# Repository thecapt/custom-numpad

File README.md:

# custom-numpad
My first keyboard pcb for a standard numpad layout. Uses a 4x5 array of MX Cherry compatable switches for better customisability over a standard 17-key numpad.
The design is based on the [discipad](https://github.com/coseyfannitutti/discipad) but was modified to use a full array and a Pro Micro 5V.

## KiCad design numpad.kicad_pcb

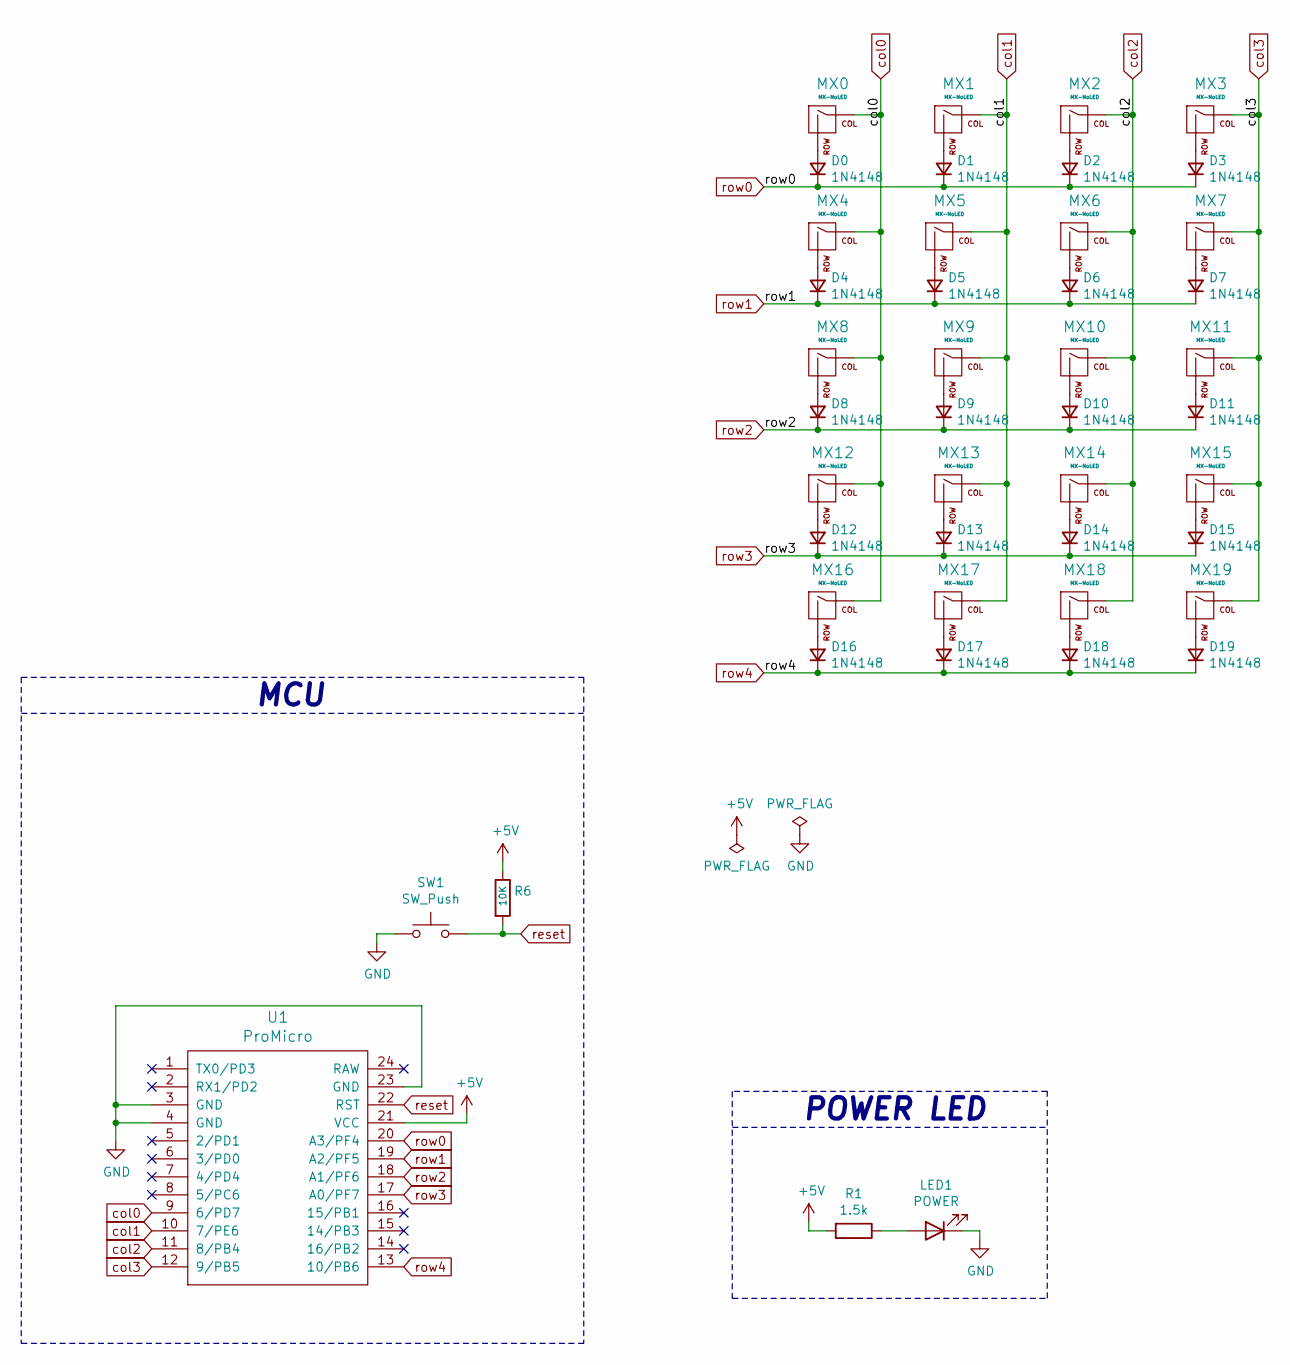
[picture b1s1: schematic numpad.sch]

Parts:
D0, D1, D2, D3, D4, D5, D6, D7, D8, D9, D10, D11, D12, D13, D14, D15, D16, D17, D18, D19: 1N4148; D_DO-35_SOD27_P5.08mm_Horizontal
LED1: POWER; LED_D3.0mm
MX0, MX1, MX2, MX3, MX4, MX5, MX6, MX7, MX8, MX9, MX10, MX11, MX12, MX13, MX14, MX15, MX16, MX17, MX18, MX19: MX-NoLED; SW_Cherry_MX_1.00u_PCB
R1: 1.5k; R_Axial_DIN0207_L6.3mm_D2.5mm_P7.62mm_Horizontal
R6: 10K; R_Axial_DIN0207_L6.3mm_D2.5mm_P7.62mm_Horizontal
SW1: SW_Push; SW_PUSH_6mm
U1: ProMicro; ArduinoProMicro

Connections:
+5V: R1.2, R6.1, U1.21 (VCC)
GND: LED1.1 (K), SW1.1, U1.3 (GND), U1.4 (GND), U1.23 (GND)
unnamed: D0.2 (A), MX0.2 (ROW)
unnamed: D1.2 (A), MX1.2 (ROW)
unnamed: D2.2 (A), MX2.2 (ROW)
unnamed: D3.2 (A), MX3.2 (ROW)
unnamed: D4.2 (A), MX4.2 (ROW)
unnamed: D5.2 (A), MX5.2 (ROW)
unnamed: D6.2 (A), MX6.2 (ROW)
unnamed: D7.2 (A), MX7.2 (ROW)
unnamed: D8.2 (A), MX8.2 (ROW)
unnamed: D9.2 (A), MX9.2 (ROW)
unnamed: D10.2 (A), MX10.2 (ROW)
unnamed: D11.2 (A), MX11.2 (ROW)
unnamed: D12.2 (A), MX12.2 (ROW)
unnamed: D13.2 (A), MX13.2 (ROW)
unnamed: D14.2 (A), MX14.2 (ROW)
unnamed: D15.2 (A), MX15.2 (ROW)
unnamed: D16.2 (A), MX16.2 (ROW)
unnamed: D17.2 (A), MX17.2 (ROW)
unnamed: D18.2 (A), MX18.2 (ROW)
unnamed: D19.2 (A), MX19.2 (ROW)
unnamed: LED1.2 (A), R1.1
col0: MX0.1 (COL), MX4.1 (COL), MX8.1 (COL), MX12.1 (COL), MX16.1 (COL), U1.9 (6/PD7)
col1: MX1.1 (COL), MX5.1 (COL), MX9.1 (COL), MX13.1 (COL), MX17.1 (COL), U1.10 (7/PE6)
col2: MX2.1 (COL), MX6.1 (COL), MX10.1 (COL), MX14.1 (COL), MX18.1 (COL), U1.11 (8/PB4)
col3: MX3.1 (COL), MX7.1 (COL), MX11.1 (COL), MX15.1 (COL), MX19.1 (COL), U1.12 (9/PB5)
reset: R6.2, SW1.2, U1.22 (RST)
row0: D0.1 (K), D1.1 (K), D2.1 (K), D3.1 (K), U1.20 (A3/PF4)
row1: D4.1 (K), D5.1 (K), D6.1 (K), D7.1 (K), U1.19 (A2/PF5)
row2: D8.1 (K), D9.1 (K), D10.1 (K), D11.1 (K), U1.18 (A1/PF6)
row3: D12.1 (K), D13.1 (K), D14.1 (K), D15.1 (K), U1.17 (A0/PF7)
row4: D16.1 (K), D17.1 (K), D18.1 (K), D19.1 (K), U1.13 (10/PB6)

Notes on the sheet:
MCU
POWER LED

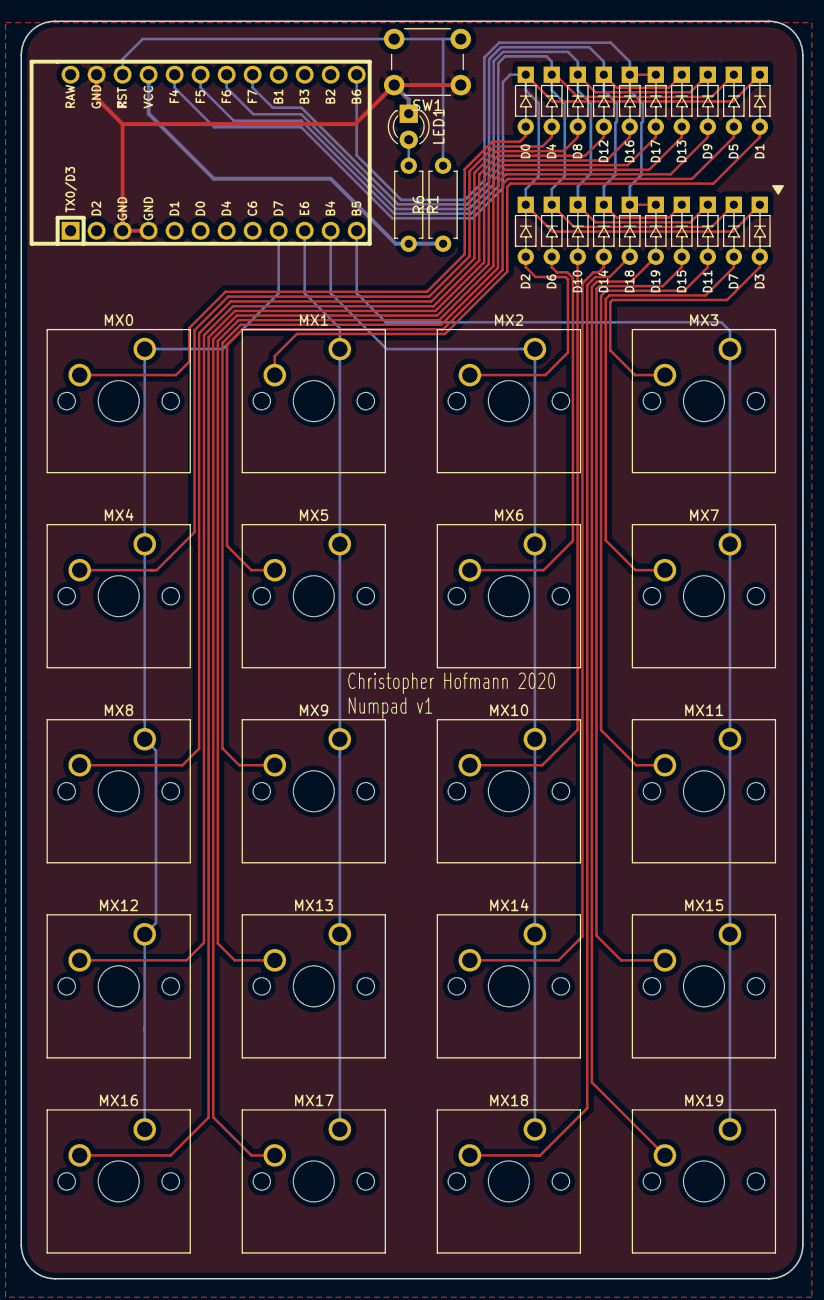
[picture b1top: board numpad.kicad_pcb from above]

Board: 2 copper layers, 76.3 x 122.8 mm, 45 parts (0 on the bottom side), 33 nets.

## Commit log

2020-07-06 Add submodules
2020-07-06 Add project libraries
2020-07-06 First version of schematic and pcb with gerbers
2020-07-06 Minor save
2020-07-12 Added QMK Firmware and configuration
